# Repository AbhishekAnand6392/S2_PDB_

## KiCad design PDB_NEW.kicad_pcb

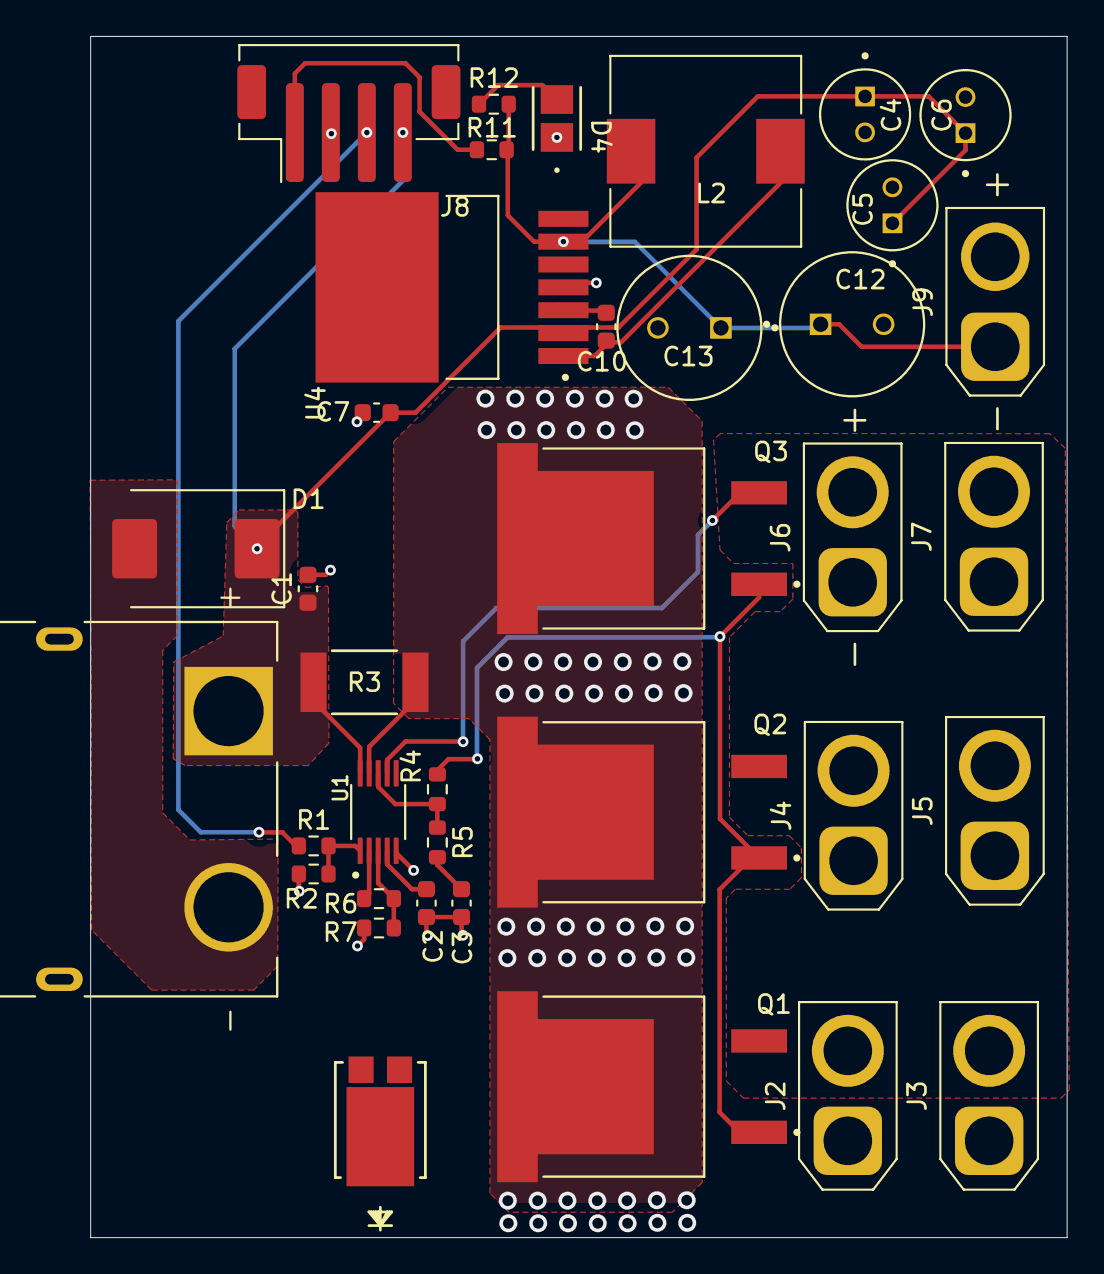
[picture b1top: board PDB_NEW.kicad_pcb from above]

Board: 4 copper layers, 54.2 x 66.7 mm, 37 parts (0 on the bottom side), 17 nets.

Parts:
C1: 0.01uF 100V; C_0603_1608Metric
C2: 10nF; C_0603_1608Metric
C3: 27nf 100v; C_0603_1608Metric
C4, C5, C6: EEUFC1H150; CAPPRD200W50D500H1100
C7, C10: C; C_0603_1608Metric
C12, C13: EEUFC1E181; CAPPRD350W60D800H1150
D1: SMC5K51A-M3_I; D_SMC
D2: D_Schottky; DIODE_TO-277A
D4: LED; APD3224ZGC-F01_KNB-M
J2, J3, J4, J5, J6, J7: Conn_01x02_Pin; AMASS_XT30U-F_1x02_P5.0mm_Vertical
J7#2: XT90PW-M; AMASS_XT90PW-M
J8: Conn_01x04_Pin; JST_PH_B4B-PH-SM4-TB_1x04-1MP_P2.00mm_Vertical
J9: Conn_01x02_Pin; AMASS_XT30U-M_1x02_P5.0mm_Vertical
L2: L; L_10.4x10.4_H4.8
Q1, Q2, Q3: PSMN3R7-100BSEJ; TRANS_PSMN3R7-100BSEJ
R1: 499k; R_0603_1608Metric
R2: 140k; R_0603_1608Metric
R3: WSLF2512L5000FEA; RES_WSLF2512_VIS-M
R4: 10 ohm; R_0603_1608Metric
R5, R11: 1k; R_0603_1608Metric
R6: 47k; R_0603_1608Metric
R7: 6.8k; R_0603_1608Metric
R12: R_US; R_0603_1608Metric
U1: TPS2490DGSR; SOP50P490X110-10N
U4: LM2678S-ADJ_NOPB; TO127P1435X464-8N

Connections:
/5V: C12.P, C13.P, J9.1, L2.2, R11.1, R12.1, U4.6 (FB)
/SENSE: Q1.MB, Q2.MB, Q3.MB, R3.2, U1.9 (SENSE)
/Switch_high: C1.1, C4.P, C5.P, C6.P, C7.1, D1.1 (K), J7#2.P (POS), J8.4, R3.1, U1.10 (VCC), U4.2 (INPUT)
/Switch_low: J8.3, R1.1
/V_OUT: D2.1 (K), J2.2, J3.2, J4.2, J5.2, J6.2, J7.2, Q1.3, Q2.3, Q3.3, U1.7 (OUT)
GND: C1.2, C2.2, C3.2, C4.N, C5.N, C6.N, C7.2, C12.N, C13.N, D1.2 (A), D2.2 (A), D4.1 (K), J2.1, J3.1, J4.1, J5.1, J6.1, J7.1, J7#2.N (NEG), J8.2, J9.2, R2.2, R7.2, U1.5 (GND), U4.4 (GND)
unnamed: C3.1, R5.2
unnamed: D4.2 (A), R12.2
unnamed: J8.1, R11.2
unnamed: Q1.1, Q2.1, Q3.1, R4.1
unnamed: R1.2, R2.1, U1.1 (EN)
unnamed: R4.2, R5.1, U1.8 (GATE)
unnamed: R6.2, R7.1, U1.3 (PROG)
unnamed: C2.1, U1.4 (TIMER)
unnamed: R6.1, U1.2 (VREF)
unnamed: C10.1, U4.3 (CB)
unnamed: C10.2, L2.1, U4.1 (SWITCH_OUTPUT)
